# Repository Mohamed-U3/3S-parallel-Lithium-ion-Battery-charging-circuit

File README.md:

# U3 LiPo Charging Circuit

A complete modular LiPo battery management solution, designed in KiCad by Eng. Mohamed Yousry. This project combines a charger, protection circuit, and active balancer for safe and efficient LiPo battery management, suited for embedded systems, robotics, and DIY electronics.

***

## Features

- **Battery Charging Circuit**
    - **IC:** BQ24090DGQ
    - Input: 5V (USB or external)
    - Integrated current setting, termination, and charging indicators
    - Optimized for single-cell LiPo batteries
- **Battery Protection Circuit**
    - **IC:** XB8889D
    - Overcharge, overdischarge, and short-circuit protection
    - Automatic recovery feature
    - Output and input connectors included for seamless integration
- **Active Balancer Circuit**
    - Balance two battery cells using autonomous active balancer ICs
    - **Inductor-based charge redistribution** for improved battery health
    - Independent status and enable pins for customization

***

## Schematic Overview

The project schematic is divided into three main sections:

1. **Battery Charging Circuit** – Handles safe charging of the LiPo cell.
2. **Battery Protection Circuit** – Protects against voltage and current faults.
3. **Active Balancer Circuit** – Maintains consistent voltage across multi-cell packs.

_All schematic design is done in KiCad 6.0 and up._

***

## Getting Started

### Prerequisites

- **KiCad** version 6.0+ (required to open Design Files)
- Basic electronics assembly and soldering skills

### Files Included

- `LiPoCharger.kicad_sch`: Complete project schematic
- (You may add: BOM, Gerber files, and 3D models if available)

### How to Use

1. **Review the schematic file** (`.kicad_sch`) in KiCad.
2. Modify component values as needed for your specific battery and current specs.
3. Generate PCB layout and fabricate your board.
4. Solder components according to schematic.
5. Integrate into your battery-powered project.

***

## Block Diagram

```
[5V Charger Input] --> [Charging Circuit] --> [Protection Circuit] --> [Active Balancer] --> [Battery Pack]
```

***

## License

This project is open-source and licensed under the MIT License. See `LICENSE` file for details.

***

## Author

**Eng. Mohamed Yousry**
Mechatronics Engineer / Embedded Hardware \& Software Designer

***

## Contribution \& Support

- Issues and pull requests are welcome!
- For questions or collaboration: mohamed.yousry0023@gmail.com

***

## Acknowledgements

- Designed using KiCad EDA 9.0.3
- Inspired by robust battery management requirements in embedded applications
- Inspired by GreatScott! Youtube channel

***

> **Disclaimer:** Double-check all component ratings for your specific application. Improper LiPo charging/protection can be dangerous.

---
<span style="display:none">[^1]</span>

<div style="text-align: center">⁂</div>

[^1]: image.jpeg

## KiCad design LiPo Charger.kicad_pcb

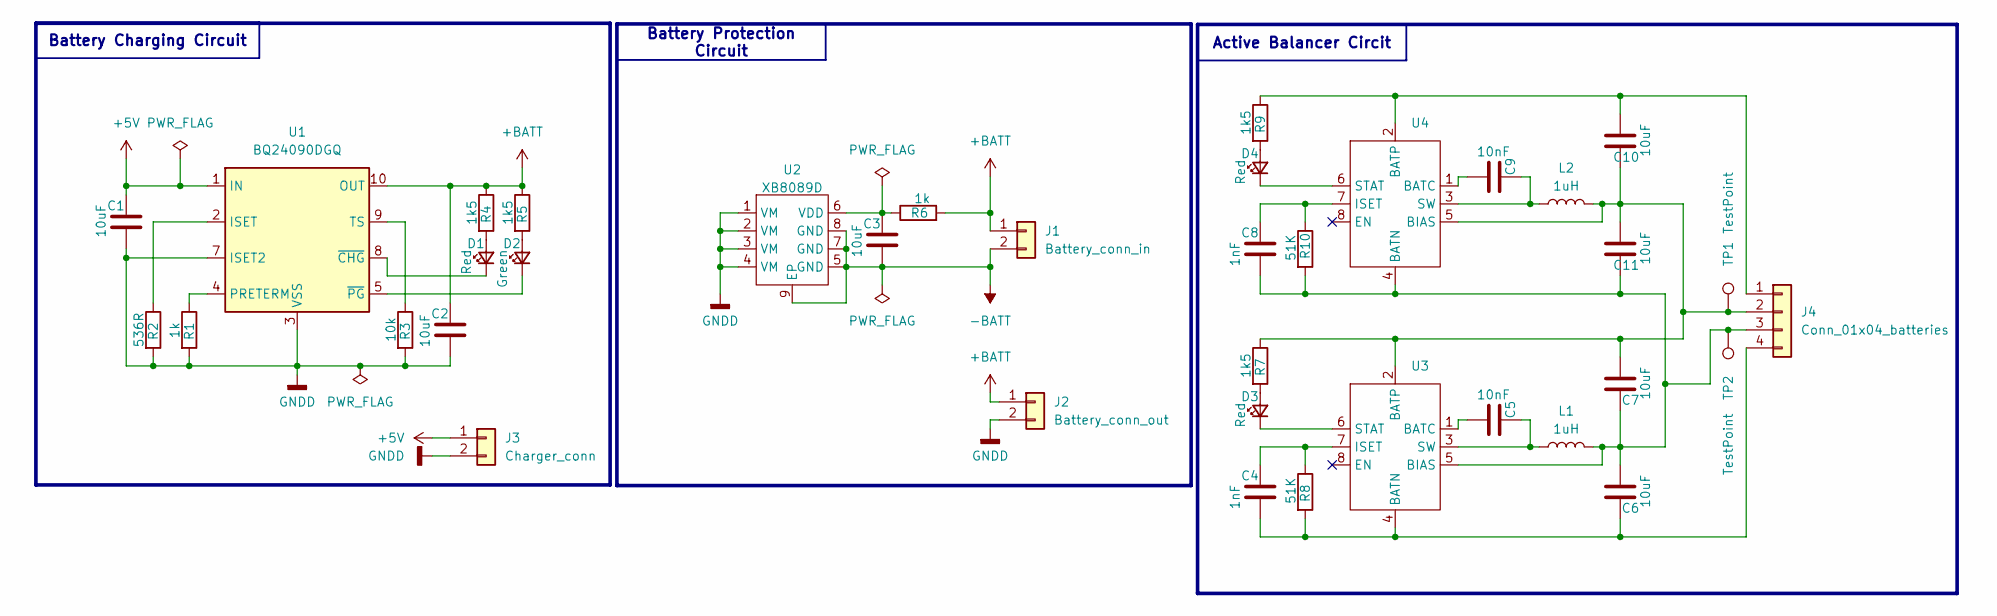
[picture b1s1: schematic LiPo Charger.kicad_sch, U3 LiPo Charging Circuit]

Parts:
C1, C2, C3, C6, C7, C10, C11: 10uF; C_0402_1005Metric_Pad0.74x0.62mm_HandSolder
C4, C8: 1nF; C_0402_1005Metric_Pad0.74x0.62mm_HandSolder
C5, C9: 10nF; C_0402_1005Metric_Pad0.74x0.62mm_HandSolder
D1, D3, D4: Red; LED_0603_1608Metric_Red
D2: Green; LED_0603_1608Metric_Green
J1: Battery_conn_in; JST_PH_B2B-PH-K_1x02_P2.00mm_Vertical
J2: Battery_conn_out; JST_PH_B2B-PH-K_1x02_P2.00mm_Vertical
J3: Charger_conn; JST_PH_B2B-PH-K_1x02_P2.00mm_Vertical
J4: Conn_01x04_batteries; JST_EH_B4B-EH-A_1x04_P2.50mm_Vertical
L1, L2: 1uH; L_Sunlord_SWPA3010S
R1, R6: 1k; R_0201_0603Metric_Pad0.64x0.40mm_HandSolder
R2: 536R; R_0201_0603Metric_Pad0.64x0.40mm_HandSolder
R3: 10k; R_0201_0603Metric_Pad0.64x0.40mm_HandSolder
R4, R5, R7, R9: 1k5; R_0201_0603Metric_Pad0.64x0.40mm_HandSolder
R8, R10: 51K; R_0201_0603Metric_Pad0.64x0.40mm_HandSolder
TP1, TP2: TestPoint; TestPoint_Pad_D1.5mm
U1: BQ24090DGQ; HVSSOP-10-1EP_3x3mm_P0.5mm_EP1.57x1.88mm_ThermalVias
U2: XB8089D; HTSOP-8-1EP_3.9x4.9mm_P1.27mm_EP2.4x3.2mm_ThermalVias
U3, U4: ETA3000; DFN-8-1EP_2x2mm_P0.5mm_EP0.6x1.2mm

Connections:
+5V: C1.1, J3.1, U1.1 (IN)
+BATT: C2.1, J1.1, J2.1, R4.1, R5.1, R6.2, U1.10 (OUT)
-BATT: C3.2, J1.2, U2.5 (GND), U2.7 (GND), U2.8 (GND), U2.9 (EP)
GNDD: C1.2, C2.2, J2.2, J3.2, R1.2, R2.2, R3.2, U1.3 (VSS), U1.7 (ISET2), U1.11 (VSS), U2.1 (VM), U2.2 (VM), U2.3 (VM), U2.4 (VM)
unnamed: D1.2 (A), R4.2
unnamed: D1.1 (K), U1.8 (~CHG)
unnamed: D2.2 (A), R5.2
unnamed: D2.1 (K), U1.5 (~PG)
unnamed: D3.2 (A), R7.2
unnamed: D3.1 (K), U3.6 (STAT)
unnamed: D4.2 (A), R9.2
unnamed: D4.1 (K), U4.6 (STAT)
unnamed: C10.2, J4.1, R9.1, U4.2 (BATP)
unnamed: C7.2, C10.1, C11.2, J4.2, L2.2, R7.1, TP1.1, U3.2 (BATP), U4.5 (BIAS)
unnamed: C6.2, C7.1, C8.2, C11.1, J4.3, L1.2, R10.2, TP2.1, U3.5 (BIAS), U4.4 (BATN)
unnamed: C4.2, C6.1, J4.4, R8.2, U3.4 (BATN)
unnamed: R2.1, U1.2 (ISET)
unnamed: R1.1, U1.4 (PRETERM)
unnamed: R3.1, U1.9 (TS)
unnamed: C3.1, R6.1, U2.6 (VDD)
unnamed: C5.2, U3.1 (BATC)
unnamed: C4.1, R8.1, U3.7 (ISET)
unnamed: C5.1, L1.1, U3.3 (SW)
unnamed: C9.2, U4.1 (BATC)
unnamed: C8.1, R10.1, U4.7 (ISET)
unnamed: C9.1, L2.1, U4.3 (SW)

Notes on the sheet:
Battery Protection Circuit
Battery Charging Circuit
Active Balancer Circit

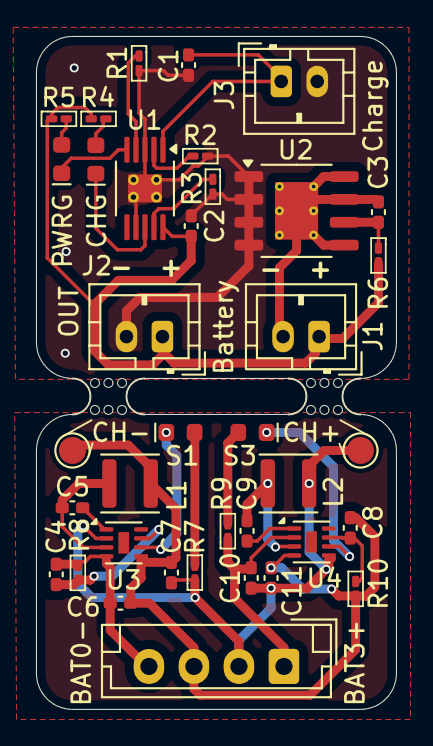
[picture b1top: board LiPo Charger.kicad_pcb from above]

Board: 2 copper layers, 20.0 x 37.4 mm, 39 parts (0 on the bottom side), 26 nets.

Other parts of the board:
mouse-bite-2mm-slot, mouse-bite-2mm-slot#2: VAL**; mouse-bite-2mm-slot

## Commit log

2025-08-12 Create .gitignore
    Create .gitignore for Kicad project
2025-08-12 adding v1.0 in the commit, Verion 1.0 is added which has single cell charging and protection circuit. next there will be an active balancer circuit in order for this single charger be able to charge 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
2025-08-12 feat: battery active balancing is now added.
2025-08-24 making production files for PCBA.
2025-09-09 doc: adding datasheets and readme file.
